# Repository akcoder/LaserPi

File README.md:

# LaserPi
LaserPi is a Raspberry Pi 2 based auxiliary controller for your laser cutter. Why would you want an auxiliary controller?

LaserPi reads sensor data (temperature, and coolant flow currently) and displays this data on the screen. You can set alarm
information based on the values from the sensors. You can be notified if the temperature goes above a user-defined value, or
if the coolant flow rate goes below a user-defined value. You can also turn on/off your chiller, exhaust, air assist pump,
and lights.

LaserPi can also act upon inputs from your laser controller. Most laser controllers have 4-5 GPIO pins that are set when
the controller is doing certain operations. For example, on the Leetro MPC-6515, output pin 4 is pulled low when the controller
is working. And output pin 1 is pulled low when the air assist box is checked for the layer.

So what can be done with these outputs? LaserPi will automatically turn on your exhaust fan when the laser controller starts
a job, and will keep the exhaust fan running for a user definable period of time after the job is finished to clear away all
the fumes. Have you ever left the air assist box checked by accident and had your air pump turn on when you didn't want it to?
I have, many times and I have to pause my machine and unplug the air assist.

## How does it work?
The brains of the operation is a Raspberry Pi with the code being Python using the QT GUI framework. Data is acquired
from the sensors, and GPIO pins on the Pi, and decisions are made.

###Sensors
*  [Waterproof 1-wire temperature sensors](http://www.aliexpress.com/wholesale?SearchText=waterproof+DS18b20)
*  [YF-S201 fluid flow sensor](http://www.dx.com/p/yf-s201-hall-effect-water-flow-counter-sensor-black-217625)

###Glue components
*  [Logic Level Converter - Bi-Directional](https://www.sparkfun.com/products/12009)
*  [Fotek SSR-25 DA Relays](http://www.amazon.com/dp/B004HZN628)

Here is a work in progress screen shot of LaserPi

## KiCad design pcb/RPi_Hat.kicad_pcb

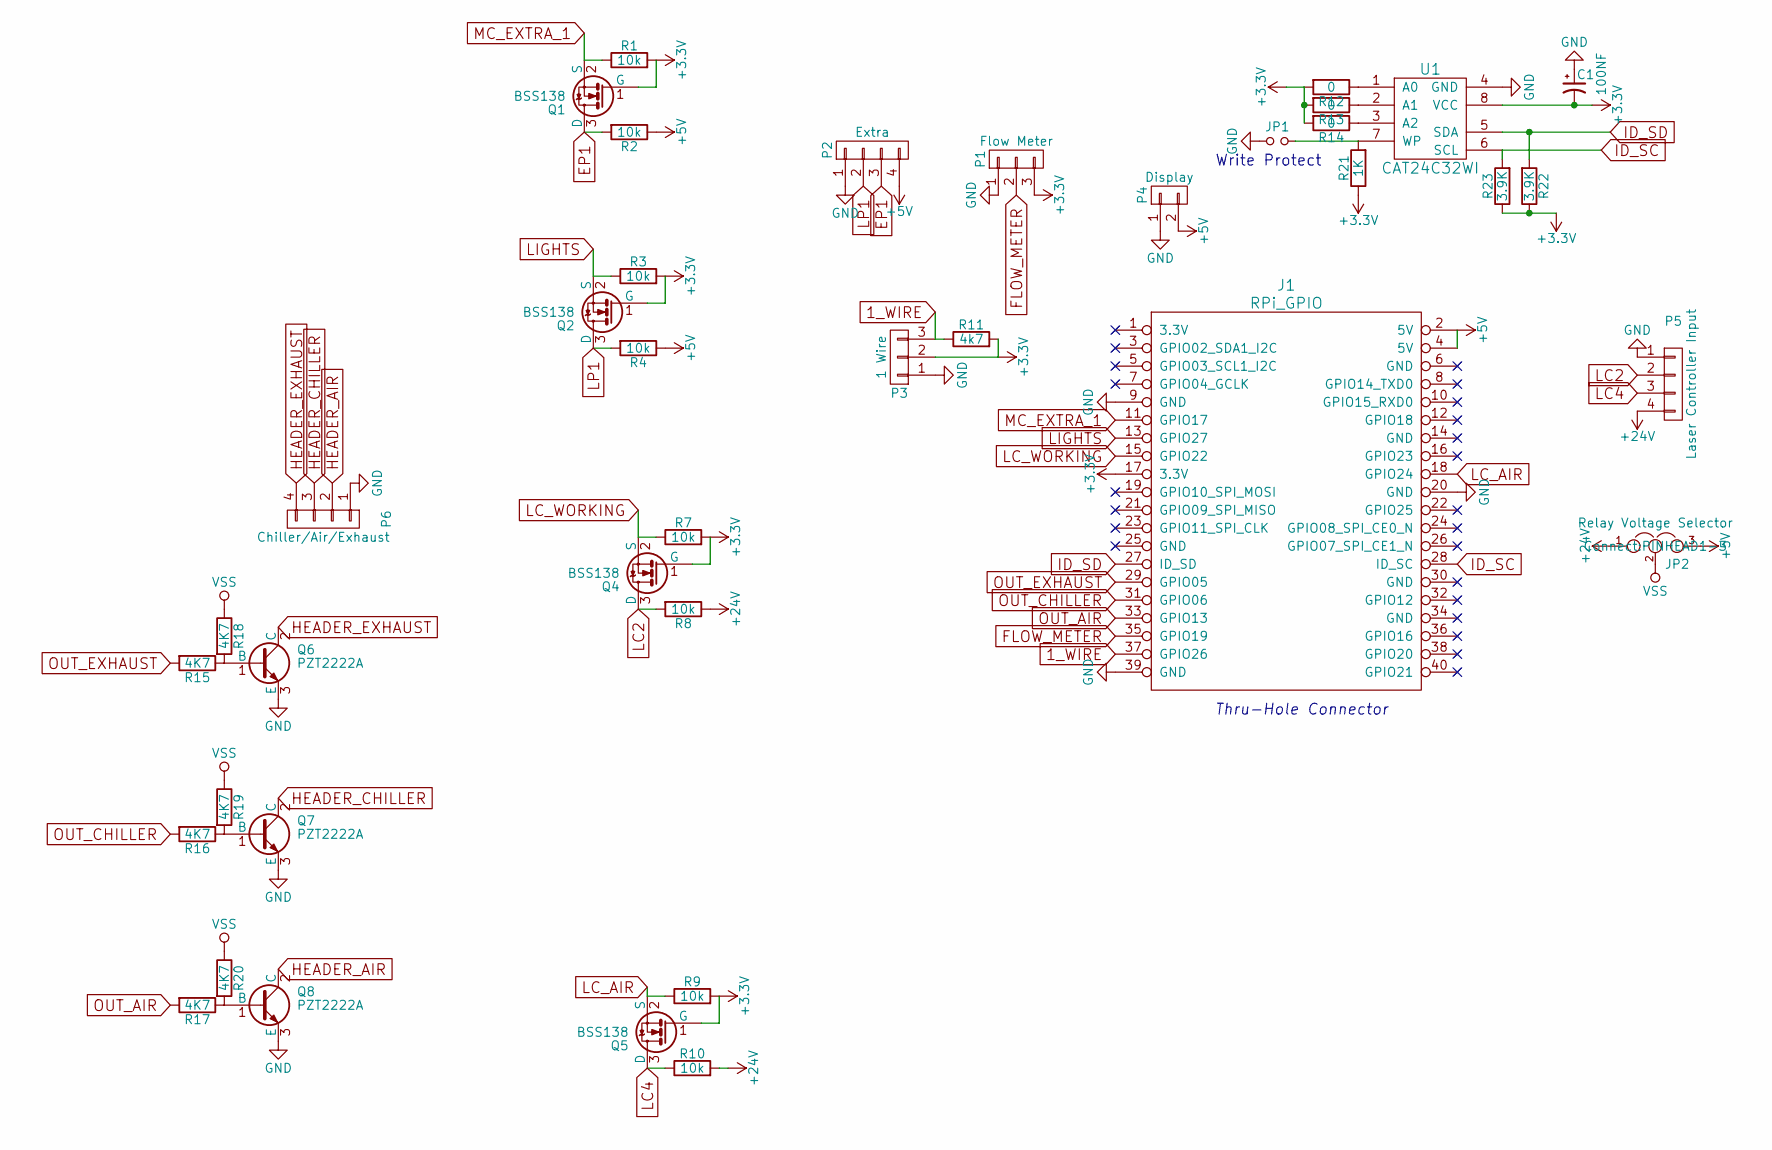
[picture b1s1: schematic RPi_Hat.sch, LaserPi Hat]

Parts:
C1: 100NF; C_1206_HandSoldering
J1: RPi_GPIO; Pin_Header_Straight_2x20
JP1: Jumper_NO_Small; PINHEAD1-2
JP2: Relay Voltage Selector; PINHEAD1-3
P1: Flow Meter; TerminalBlock_Pheonix_MPT-2.54mm_3pol
P2: Extra; TerminalBlock_Pheonix_MPT-2.54mm_4pol
P3: 1 Wire; TerminalBlock_Pheonix_MPT-2.54mm_3pol
P4: Display; TerminalBlock_Pheonix_MPT-2.54mm_2pol
P5: Laser Controller Input; TerminalBlock_Pheonix_MPT-2.54mm_4pol
P6: Chiller/Air/Exhaust; TerminalBlock_Pheonix_MPT-2.54mm_4pol
Q1, Q2, Q4, Q5: BSS138; SOT-23
Q6, Q7, Q8: PZT2222A; SOT-23
R1, R2, R3, R4, R7, R8, R9, R10: 10k; R_1206_HandSoldering
R11: 4k7; R_1206_HandSoldering
R12, R13, R14: 0; R_0402
R15, R16, R17, R18, R19, R20: 4K7; R_1206_HandSoldering
R21: 1K; R_1206_HandSoldering
R22, R23: 3.9K; R_1206_HandSoldering
U1: CAT24C32WI; SOIC-8-N

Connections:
1_WIRE: J1.37 (GPIO26), P3.3, R11.1
+3V3: C1.2, J1.17 (3.3V), P1.3, P3.2, Q1.1 (G), Q2.1 (G), Q4.1 (G), Q5.1 (G), R1.2, R3.2, R7.2, R9.2, R11.2, R12.2, R13.2, R14.2, R21.1, R22.1, R23.1, U1.8 (VCC)
+5V: J1.2 (5V), J1.4 (5V), JP2.3, P2.4, P4.2, R2.1, R4.1
+24V: JP2.1, P5.4, R8.1, R10.2
EP1: P2.3, Q1.3 (D), R2.2
FLOW_METER: J1.35 (GPIO19), P1.2
GND: C1.1, J1.9 (GND), J1.20 (GND), J1.39 (GND), JP1.1, P1.1, P2.1, P3.1, P4.1, P5.1, P6.1, Q6.3 (E), Q7.3 (E), Q8.3 (E), U1.4 (GND)
HEADER_AIR: P6.2, Q8.2 (C)
HEADER_CHILLER: P6.3, Q7.2 (C)
HEADER_EXHAUST: P6.4, Q6.2 (C)
ID_SC: J1.28 (ID_SC), R23.2, U1.6 (SCL)
ID_SD: J1.27 (ID_SD), R22.2, U1.5 (SDA)
LC2: P5.2, Q4.3 (D), R8.2
LC4: P5.3, Q5.3 (D), R10.1
LC_AIR: J1.18 (GPIO24), Q5.2 (S), R9.1
LC_WORKING: J1.15 (GPIO22), Q4.2 (S), R7.1
LIGHTS: J1.13 (GPIO27), Q2.2 (S), R3.1
LP1: P2.2, Q2.3 (D), R4.2
MC_EXTRA_1: J1.11 (GPIO17), Q1.2 (S), R1.1
unnamed: JP1.2, R21.2, U1.7 (WP)
unnamed: Q6.1 (B), R15.1, R18.2
unnamed: Q7.1 (B), R16.1, R19.2
unnamed: Q8.1 (B), R17.1, R20.2
unnamed: R12.1, U1.1 (A0)
unnamed: R13.1, U1.2 (A1)
unnamed: R14.1, U1.3 (A2)
OUT_AIR: J1.33 (GPIO13), R17.2
OUT_CHILLER: J1.31 (GPIO06), R16.2
OUT_EXHAUST: J1.29 (GPIO05), R15.2
VSS: JP2.2, R18.1, R19.1, R20.1

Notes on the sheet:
Thru-Hole Connector
Write Protect

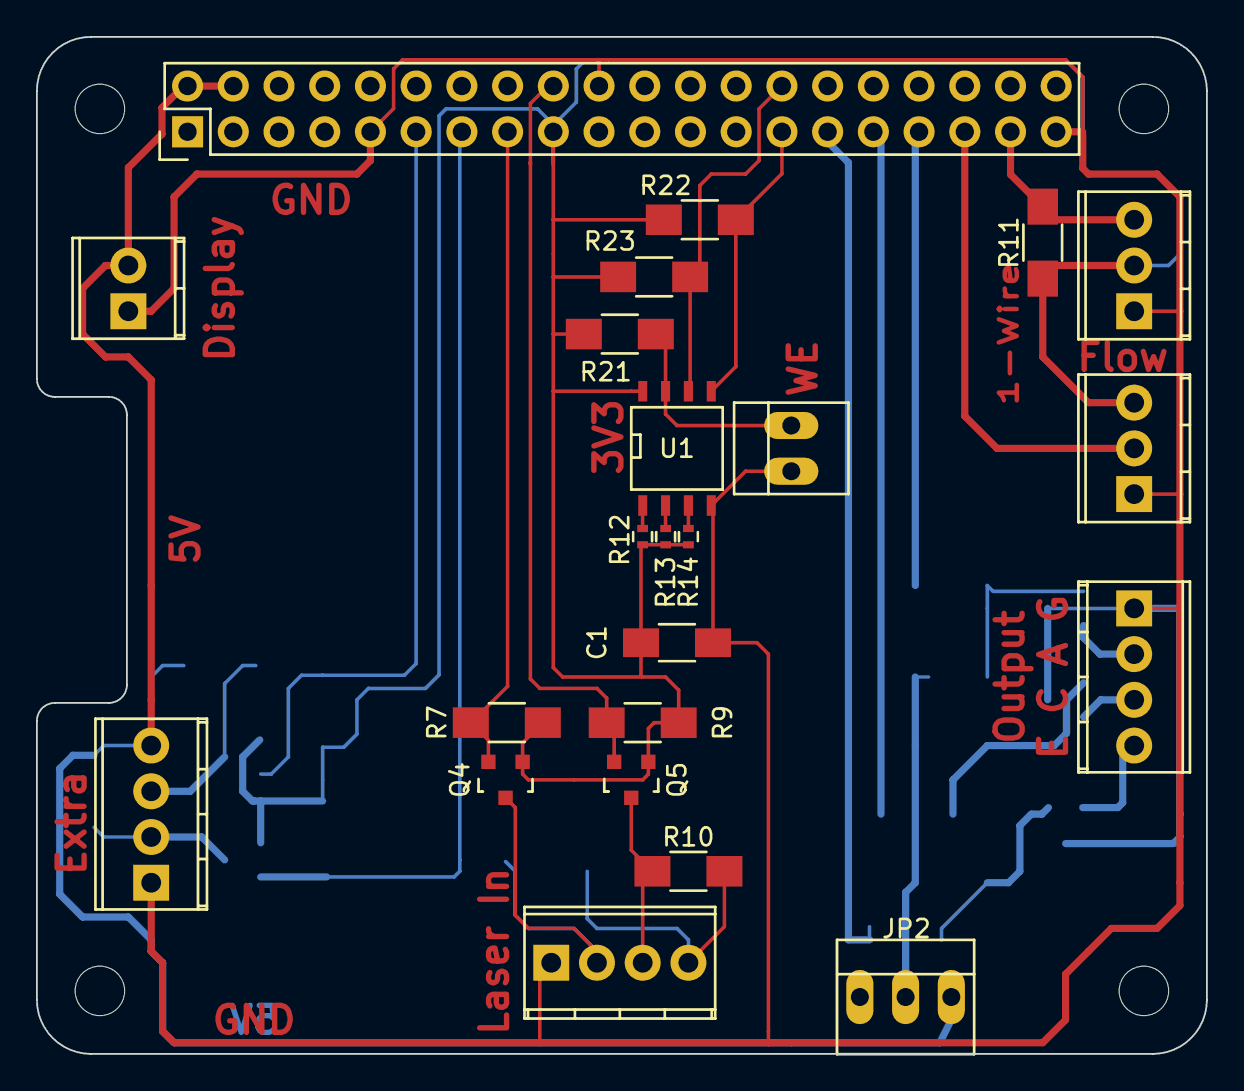
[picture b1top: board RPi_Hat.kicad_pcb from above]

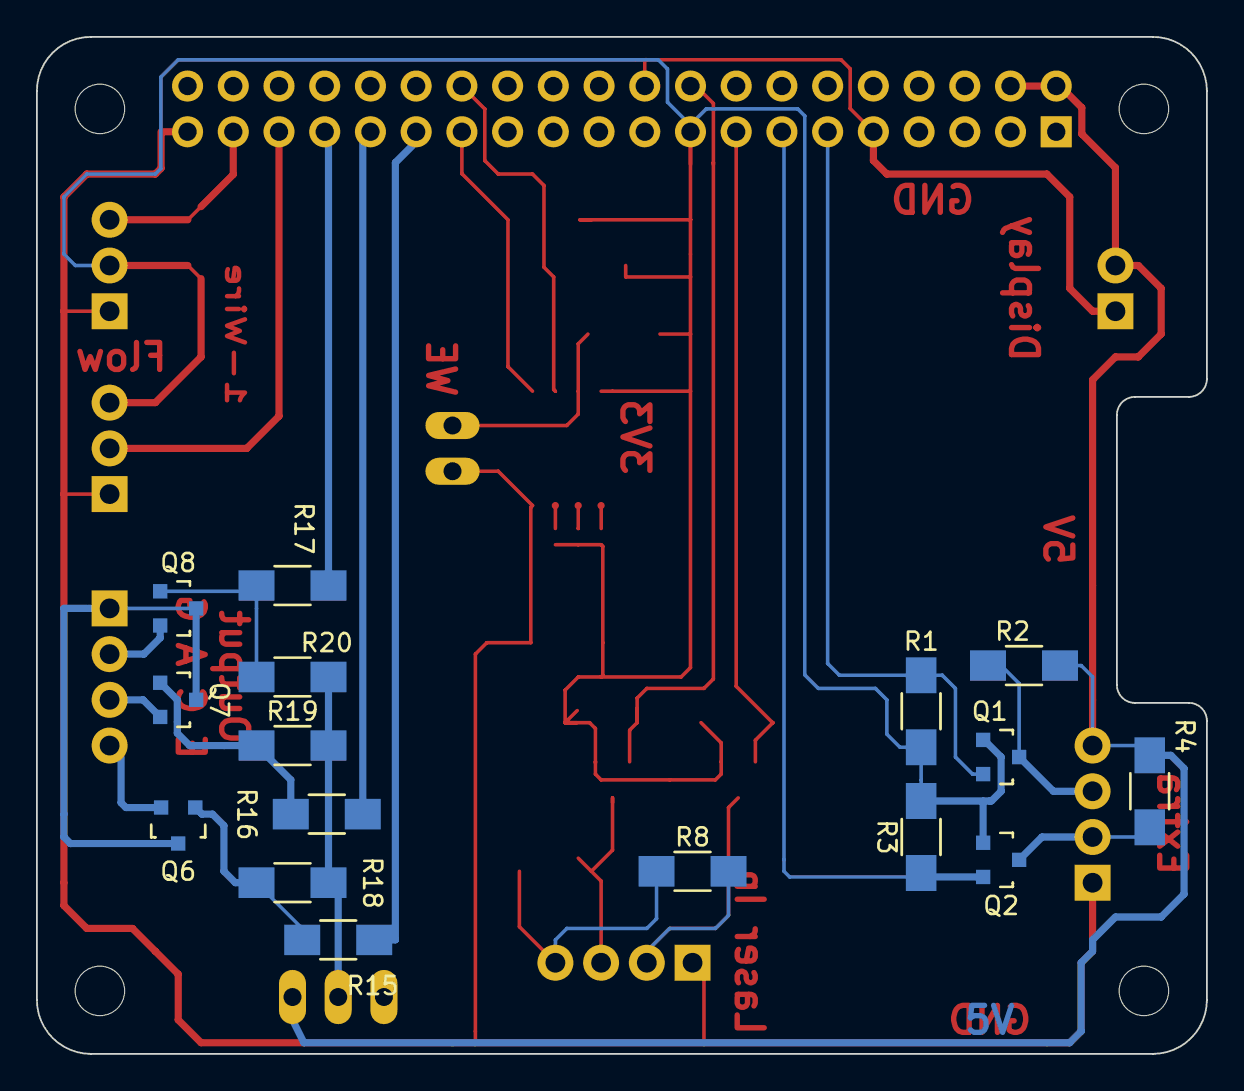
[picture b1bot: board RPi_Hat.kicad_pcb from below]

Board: 2 copper layers, 65.0 x 56.5 mm, 39 parts (16 on the bottom side), 30 nets.

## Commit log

2016-02-28 Initial import
2016-02-29 - Add exit button - Make exiting the app cleanup the GPIO - Misc pylint cleanups - Trigger more GPIOs - Figure out the final pin configuration
2016-02-29 Move the shutdown code out of the view model and into the controller where it should be.
2016-03-05 Add Temperature and FlowMeter support Add settings support
2016-03-05 Automate setup
2016-03-05 Add support for configurable exhaust post roll
2016-03-05 Remove extraneous parenthesizes
2016-03-06 Make Settings access easier
2016-03-06 Rename LaserPi -> LaserPiPy
2016-03-06 LaserPiIot initial commit
2016-03-06 Add the LaserPiPy project files
2016-03-07 Cleanup the GPIO setup Make the routed commands work by setting up the dispatcher
2016-03-09 Remove the Windows IoT version
2016-03-09 Move the src to the src dir
2016-03-09 Cleanup the instructions a little bit
2016-03-09 Add some notes to the readme
2016-03-09 Add some standard files
    Remove some entries no longer needed in the .gitignore file and add the
    gitattributes file
2016-03-10 Update the readme
2016-03-10 Dynamically load the temperature sensors from the config and add them to the display Do a fade in animation when the temp is first set in the view
2016-03-10 Make the fade in animation a little longer
2016-03-11 Setup flow rate sensor
    Setup the flow rate sensor
    Don't use a property on the view model to hold the degree symbol, put it
    in the Temperature.js file
2016-03-11 Show units for temperature
    Don't do all the rejiggering of the config json to and from an object to
    put it into the QML.
2016-03-12 Fix layout issues, temp changes
    Fix some layout nits
    Put the degree symbol and temp units in their own label and right align
    the temperature
2016-03-12 Vertically align all the labels to v center
2016-03-12 Use factory to create sensors
    Use the factory pattern to create the sensors, and pass the config into
    the sensors.
2016-03-12 Globals are bad!
    Get rid of all the globals in Temperature.js by using lambdas!
2016-03-12 Cleanup temperature view
    Make the temperature view more generic
    Remove the model from the temperature view and set properties on the
    view
2016-03-12 More cleanup
    Move the units into the sensor item. This allows you to have different
    units on a per sensor basis.
    Wire up the flow meter sensor
2016-03-12 Add sanity checking to the units display/conversion
2016-03-13 Rename the docs folder
    Rename Documentation -> docs
2016-03-13 Add a setup file
2016-03-13 Make the setup file executable
2016-03-13 Cleanup
    Now that we have the setup file, delete the "Linux" folder
2016-03-13 Cleanup
2016-03-13 Cleanup, grr!
2016-03-13 Add threshold colors to the flow meter
2016-03-14 Switch from print to logging
2016-03-14 Remove commented out code
2016-03-14 Remove test log message
2016-03-14 Use loops for gpio setup
2016-04-03 Switch the 1 wire GPIO
    From the default of pin 4 to 26. This works out better for the pcb
2016-04-03 Remove unneeded config
2016-04-03 Fix the temp threshold values
2016-04-03 Pi HAT
    Pi HAT schematic and PCB done in KiCAD
2016-04-04 Make PCB layout cleaner
    Swap some things around to make the layout cleaner
2016-04-05 Schematic updates
    Don't use a relay, use a level shifter so the pin can be used as either
    an input or an output.
2016-04-14 Add outputs
    for the chiller, exhaust, air
2016-04-15 Add passives for the EEPROM
2016-04-16 Update the schematic and board files
2016-04-19 Add labels to pcb
2016-05-05 Adjust flow-meter correction factor
2016-08-12 Update the schematic
